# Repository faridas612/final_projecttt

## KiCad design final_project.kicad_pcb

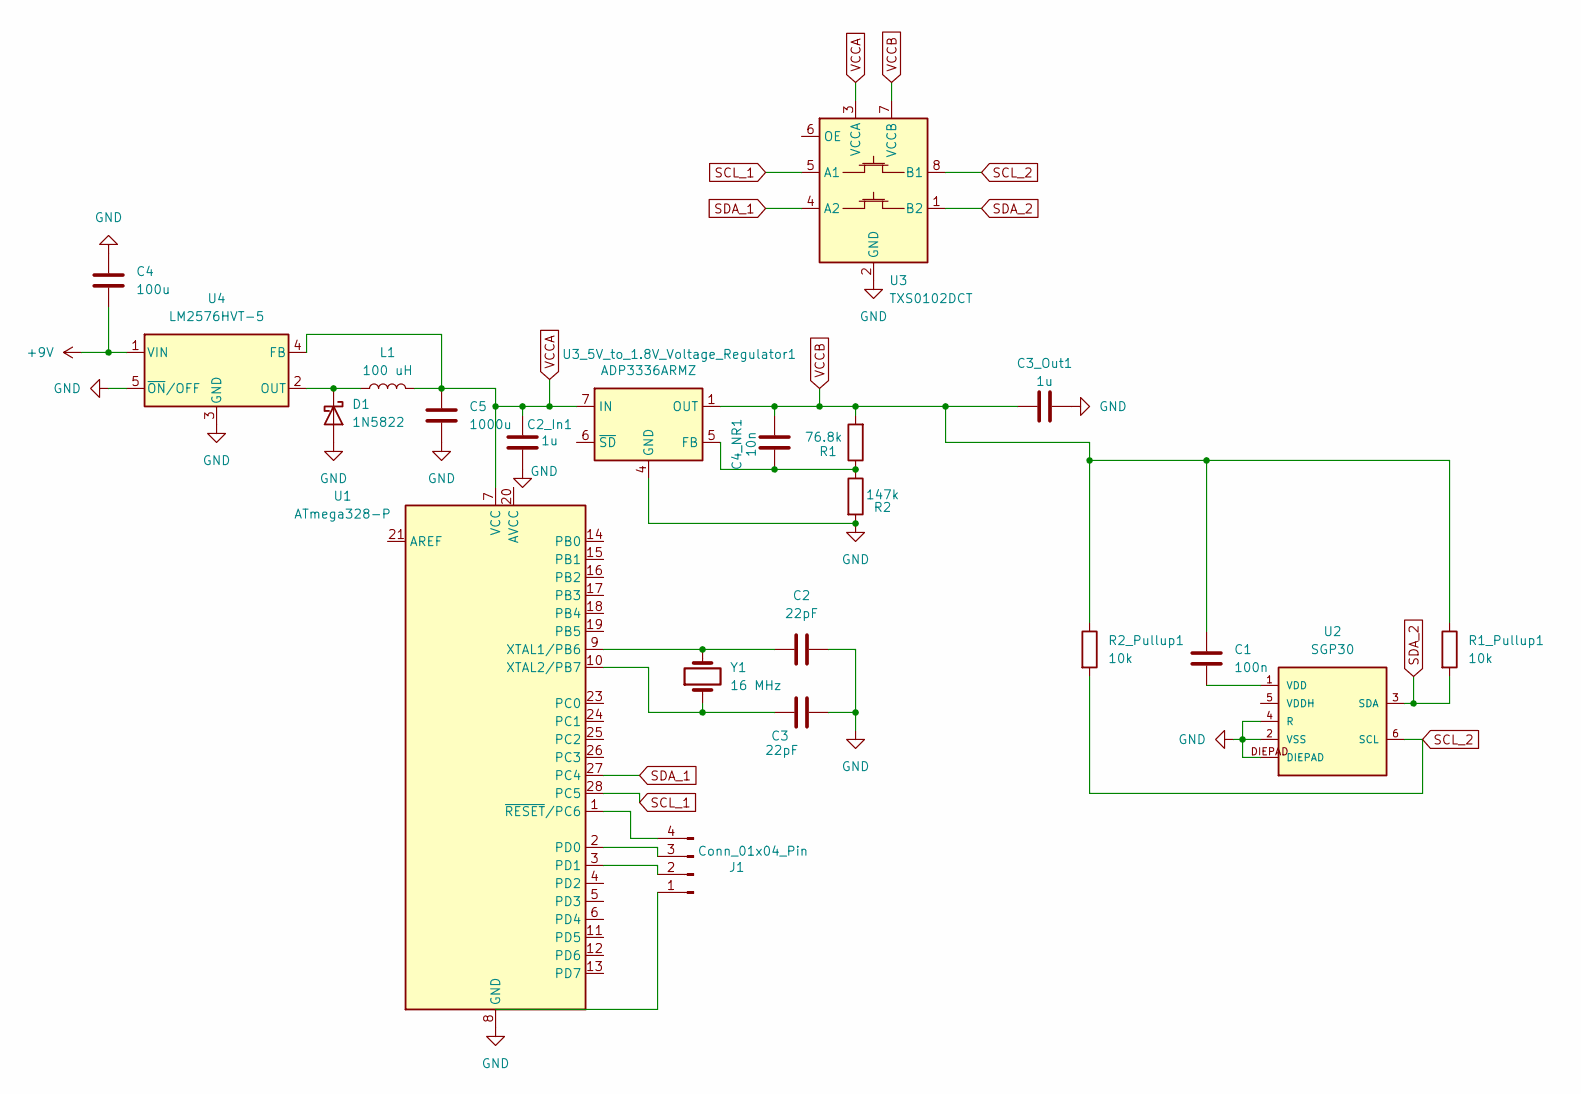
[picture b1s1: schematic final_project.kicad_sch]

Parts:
C1: 100n; CAPC0402X22N
C2, C3: 22pF; CAPC17595_87N_KEM-M
C2_In1, C3_Out1: 1u; CAP_CL10_SAM-M
C4: 100u; CAP_GRM31_1206_MUR-M
C4_NR1: 10n; G-155_MUR
C5: 1000u
D1: 1N5822; D_DO-201AD_P15.24mm_Horizontal
J1: Conn_01x04_Pin; PinHeader_1x04_P1.00mm_Vertical
L1: 100 uH; IND_TAIYO_BRL3225_TAY
R1: 76.8k; YAG_MF25_YAG
R1_Pullup1, R2_Pullup1: 10k; YAG_MF25_YAG
R2: 147k; YAG_MF25_YAG
U1: ATmega328-P; DIP-28_W7.62mm
U2: SGP30
U3: TXS0102DCT; SSOP-8_2.95x2.8mm_P0.65mm
U3_5V_to_1.8V_Voltage_Regulator1: ADP3336ARMZ; MSOP-8_3x3mm_P0.65mm
U4: LM2576HVT-5; TO-220-5_Vertical
Y1: 16 MHz; XTAL_ECS-160-20-5PX-TR

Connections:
+9V: C4.2, U4.1 (VIN)
GND: C2.2, C2_In1.2, C3.1, C3_Out1.2, C4.1, C5.2, D1.2 (A), R2.2, U1.8 (GND), U1.22 (GND), U2.2 (VSS), U2.4 (R), U2.DIEPAD, U3.2 (GND), U3_5V_to_1.8V_Voltage_Regulator1.4 (GND), U4.3 (GND), U4.5 (~ON/OFF)
unnamed: D1.1 (K), L1.1, U4.2 (OUT)
unnamed: J1.2, U1.3 (PD1)
unnamed: J1.3, U1.2 (PD0)
unnamed: J1.4, U1.1 (~RESET/PC6)
unnamed: C2.1, U1.9 (XTAL1/PB6), Y1.2
unnamed: C3.2, U1.10 (XTAL2/PB7), Y1.1
unnamed: C1.2, U2.1 (VDD)
unnamed: C4_NR1.1, R1.1, R2.1, U3_5V_to_1.8V_Voltage_Regulator1.5 (FB)
SCL_1: U1.28 (PC5), U3.5 (A1)
SCL_2: R2_Pullup1.2, U2.6 (SCL), U3.8 (B1)
SDA_1: U1.27 (PC4), U3.4 (A2)
SDA_2: R1_Pullup1.2, U2.3 (SDA), U3.1 (B2)
VCCA: C2_In1.1, C5.1, L1.2, U1.7 (VCC), U3.3 (VCCA), U3_5V_to_1.8V_Voltage_Regulator1.7 (IN), U3_5V_to_1.8V_Voltage_Regulator1.8 (IN), U4.4 (FB)
VCCB: C1.1, C3_Out1.1, C4_NR1.2, R1.2, R1_Pullup1.1, R2_Pullup1.1, U3.7 (VCCB), U3_5V_to_1.8V_Voltage_Regulator1.1 (OUT), U3_5V_to_1.8V_Voltage_Regulator1.2 (OUT), U3_5V_to_1.8V_Voltage_Regulator1.3 (OUT)

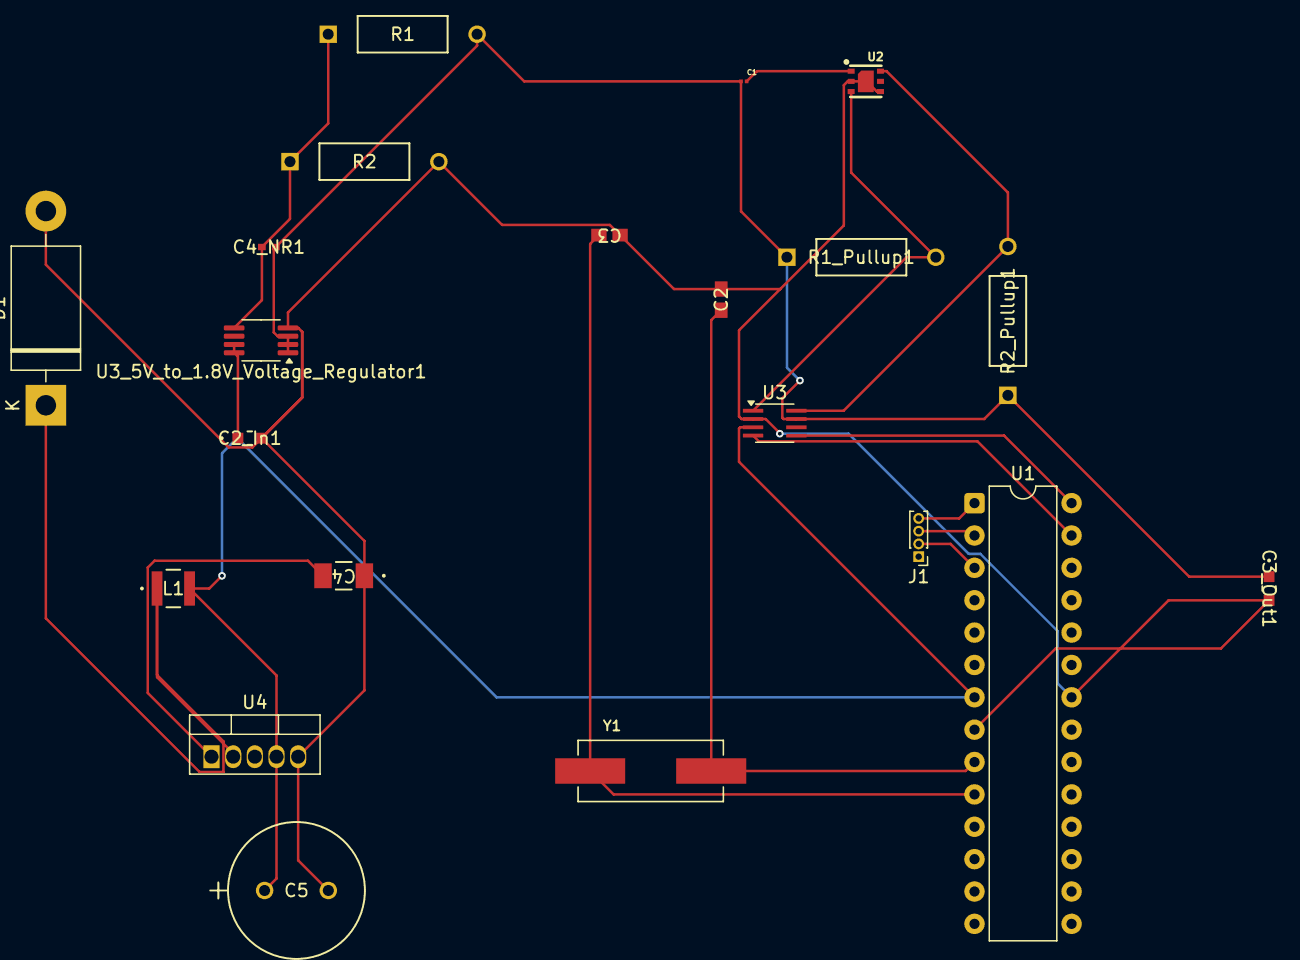
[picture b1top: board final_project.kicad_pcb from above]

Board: 2 copper layers, 21 parts (0 on the bottom side), 16 nets.

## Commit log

2025-04-22 blah blah
2025-04-22 Added Atmega328-P
2025-04-22 Added SGP30 Sensor
2025-04-22 Added GND to SGP30 sensor
2025-04-24 Updated PCB Design
2025-04-24 Added Voltage Regulator
2025-04-24 Added a bidirectional level shifter
2025-04-25 Added Global labels
    Added Global labels to the level shifter to make it more organized.
2025-04-25 Added the oscillator for Atmega
2025-04-25 Added the battery
2025-04-29 Added USB Connections
2025-04-29 Annotated Schematic
2025-04-29 Added Footprints
2025-04-29 Add Libraries
2025-04-29 Added C100uF
2025-04-29 Added Capacitor Library
2025-04-29 Added Inductor Library
2025-04-29 Added Crystal Footprint Library
2025-04-29 Added 1000uF capacitor
2025-04-29 Footprint Library Completed
2025-04-29 Started PCB board from Schematic
2025-04-29 Untangled PCB Design
2025-04-29 Saved Design
2025-04-29 Saved Design Again
2025-05-01 Wire Connections to PCB
